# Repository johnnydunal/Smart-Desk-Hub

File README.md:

# Smart Desk Hub

### Overview
The Smart Desk Hub is an ambient smart desktop display station powered by an E-Paper display and an ESP32 microcontroller. It presents time, weather, room metrics, and calendar events at a glance, featuring a dual-tier local/cloud voice assistant for hands-free productivity and task automation.

### Hardware Components
- Microcontroller: ESP32 (The brain of the hub)
- Audio Input: INMP441 I2S Omnidirectional Microphone
- Audio Output: MAX98357A I2S Speaker Amplifier
- Environmental Sensor: Adafruit BME280 (Temperature, Humidity, Pressure)
- Display: 4.2inch Waveshare E-Ink display module

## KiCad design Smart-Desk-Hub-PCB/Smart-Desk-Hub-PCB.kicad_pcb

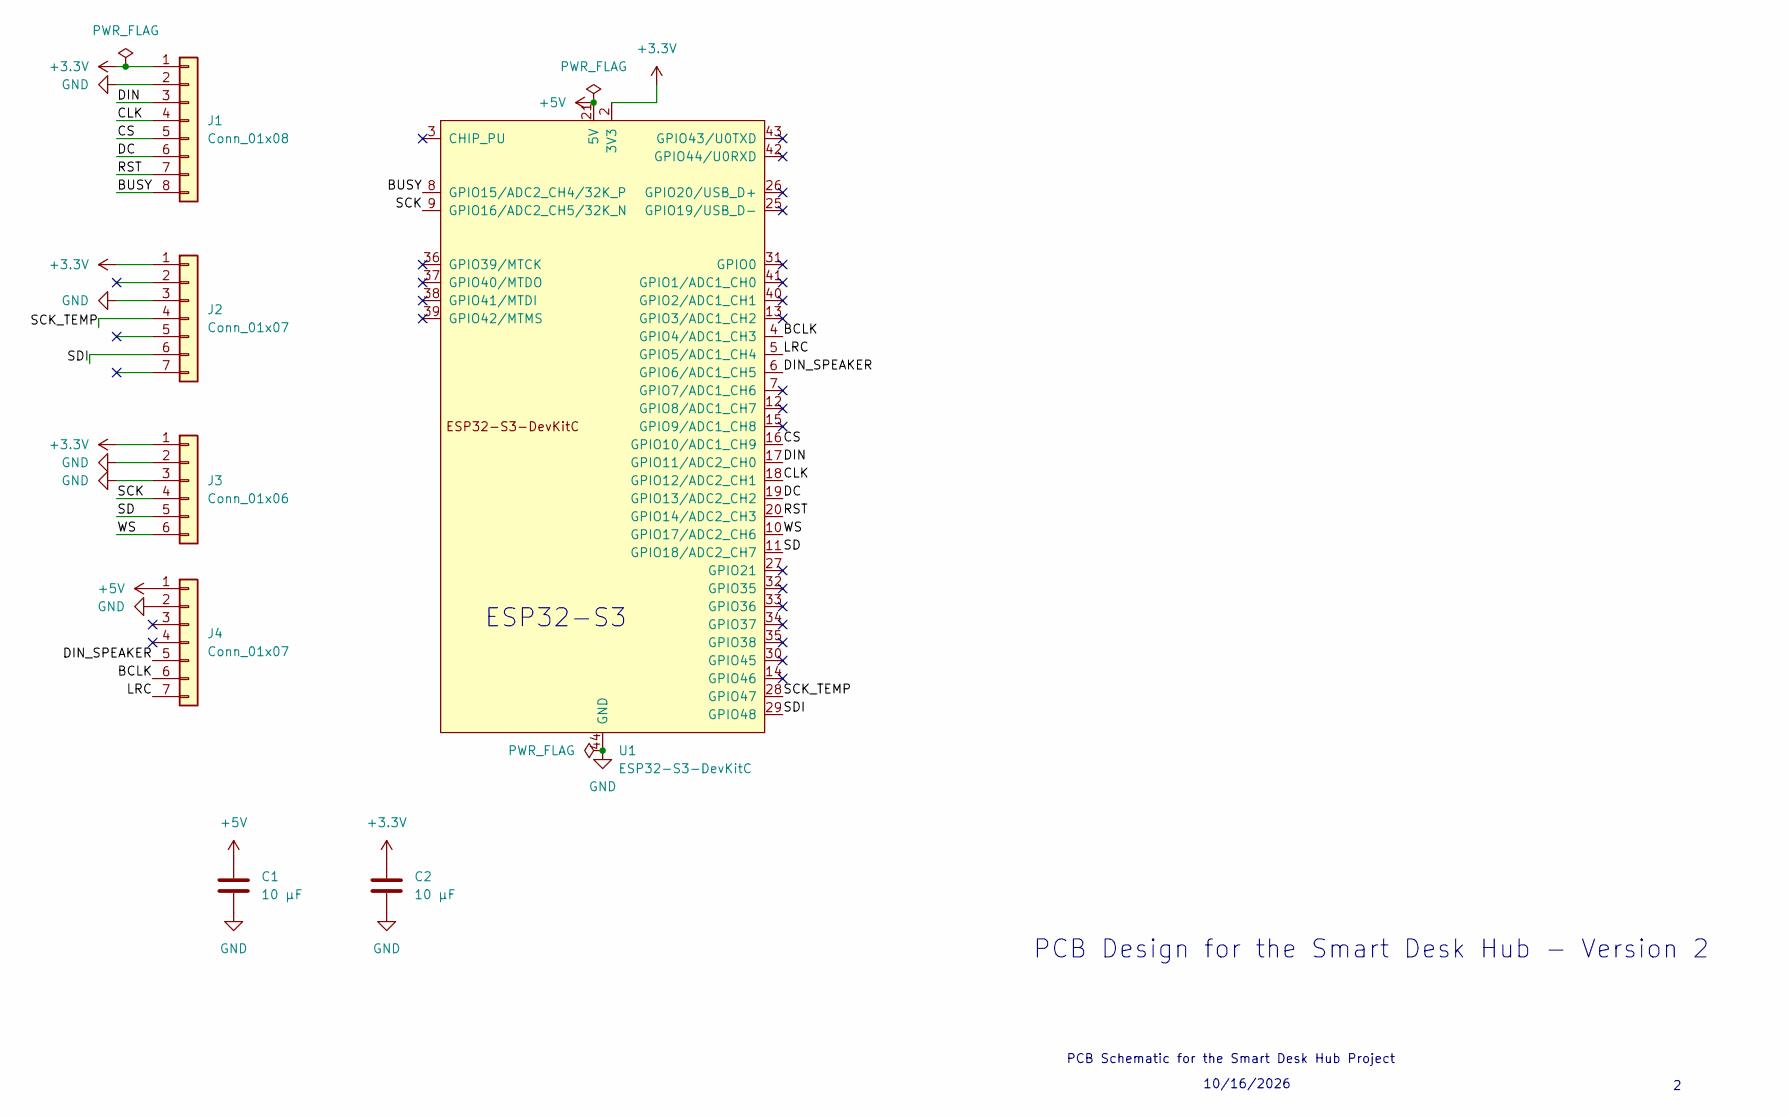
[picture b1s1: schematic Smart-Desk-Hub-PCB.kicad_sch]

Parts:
C1, C2: 10 µF; C_0805_2012Metric_Pad1.18x1.45mm_HandSolder
J1: Conn_01x08; PinHeader_1x08_P2.54mm_Vertical
J2, J4: Conn_01x07; PinHeader_1x07_P2.54mm_Vertical
J3: Conn_01x06; PinHeader_1x06_P2.54mm_Vertical
U1: ESP32-S3-DevKitC

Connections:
+3.3V: C2.1, J1.1, J2.1, J3.1, U1.1 (3V3), U1.2 (3V3)
+5V: C1.1, J4.1, U1.21 (5V)
/BCLK: J4.6, U1.4 (GPIO4/ADC1_CH3)
/BUSY: J1.8, U1.8 (GPIO15/ADC2_CH4/32K_P)
/CLK: J1.4, U1.18 (GPIO12/ADC2_CH1)
/CS: J1.5, U1.16 (GPIO10/ADC1_CH9)
/DC: J1.6, U1.19 (GPIO13/ADC2_CH2)
/DIN: J1.3, U1.17 (GPIO11/ADC2_CH0)
/DIN_SPEAKER: J4.5, U1.6 (GPIO6/ADC1_CH5)
/LRC: J4.7, U1.5 (GPIO5/ADC1_CH4)
/RST: J1.7, U1.20 (GPIO14/ADC2_CH3)
/SCK: J3.4, U1.9 (GPIO16/ADC2_CH5/32K_N)
/SCK_TEMP: J2.4, U1.28 (GPIO47)
/SD: J3.5, U1.11 (GPIO18/ADC2_CH7)
/SDI: J2.6, U1.29 (GPIO48)
/WS: J3.6, U1.10 (GPIO17/ADC2_CH6)
GND: C1.2, C2.2, J1.2, J2.3, J3.2, J3.3, J4.2, U1.22 (GND), U1.23 (GND), U1.24 (GND), U1.44 (GND)

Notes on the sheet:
PCB Schematic for the Smart Desk Hub Project
10/16/2026
PCB Design for the Smart Desk Hub - Version 2
ESP32-S3

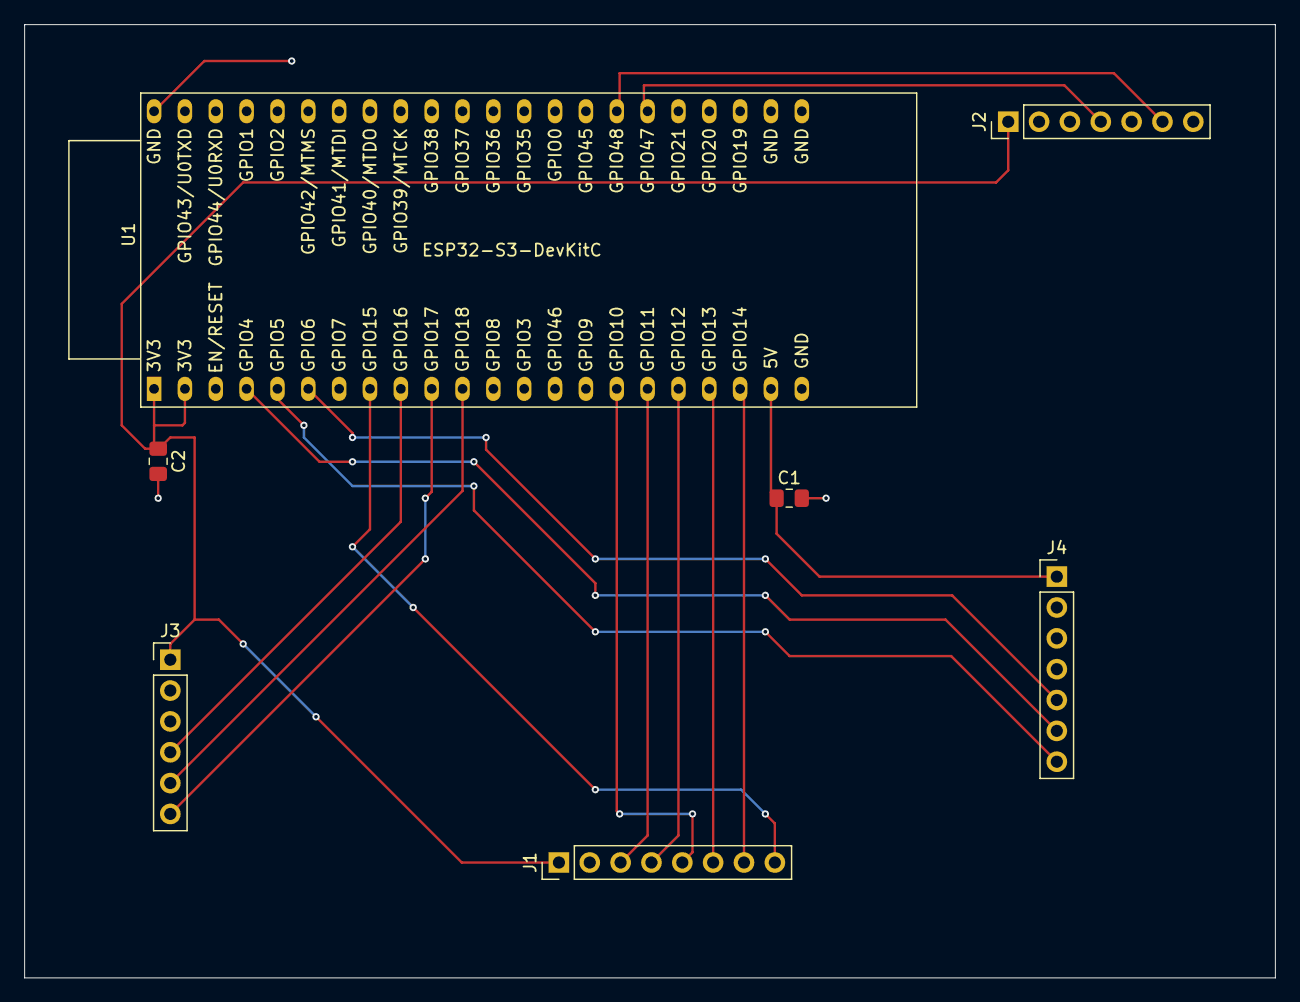
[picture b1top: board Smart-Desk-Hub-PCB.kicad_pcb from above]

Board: 2 copper layers, 103.0 x 78.5 mm, 7 parts (0 on the bottom side), 17 nets.
